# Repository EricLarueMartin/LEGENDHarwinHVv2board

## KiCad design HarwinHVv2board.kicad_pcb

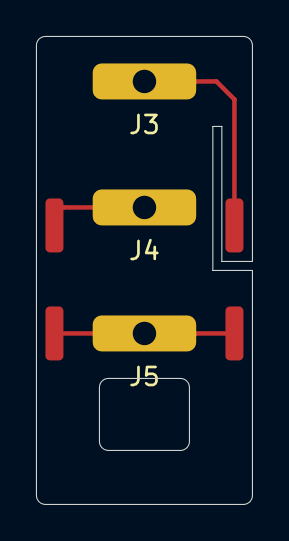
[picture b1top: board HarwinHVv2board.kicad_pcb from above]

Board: 2 copper layers, 12.0 x 26.0 mm, 7 parts (0 on the bottom side), 3 nets.

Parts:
J1: HV2; SolderWirePad_1x01_SMD_1x3mm
J2: GND2; SolderWirePad_1x01_SMD_1x3mm
J3: HarwinHV1; Pin_D1.3mm_L5.75mmW2.0mm
J4: HarwinHV2; Pin_D1.3mm_L5.75mmW2.0mm
J5: HarwinGND; Pin_D1.3mm_L5.75mmW2.0mm
J6: HV1; SolderWirePad_1x01_SMD_1x3mm
J7: GND1; SolderWirePad_1x01_SMD_1x3mm

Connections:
unnamed: J1.1, J4.1
unnamed: J2.1, J5.1, J7.1
unnamed: J3.1, J6.1

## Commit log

2020-07-06 Initial commit. The Harwin sockets need to be replaced with the proper footprint, currently just using a square pad with a 1.25mm hole.
2020-07-06 Changed Harwin connector pads to 1.3mm drill hole on a 5.75 x 2 mm rectangular pad with rounded corners.
2020-07-07 Modified to use Harwin socket STEP file. Generated STEP file of board with sockets and traces on 1.6 mm PCB.
